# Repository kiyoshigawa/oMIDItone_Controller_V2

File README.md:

This is a refactored and updated version of the code in the https://github.com/kiyoshigawa/oMIDItone github repo intended to simplify and make faster the existing code base while simultaneously switching to PlatformIO.

It is code written to run a 6-head MIDI controlled Otamatone synth, including lighting and mouth opening/closing servo animations. The project is running on a Teensy 3.2, using the arduino framework through PlatformIO, and is using the following libraries in addition to the libraries that I have written myself specifically for this project:
https://github.com/adafruit/Adafruit_NeoPixel 
https://github.com/adafruit/Adafruit-PWM-Servo-Driver-Library (Modified to work with i2c_t3.h)
https://github.com/nox771/i2c_t3
https://github.com/pedvide/ADC

The updated version is reworked to make handling MIDI it's own MIDIController class, as well as to simplify the oMIDItone object class to operate based only on desired frequencies instead of handling MIDI notes, pitch bends, etc.

This readme information will be lagging behind the actual development of the code base until it is nearly done and working properly, so look for more up-to-date comments in the source files for the time being. Once the project is working properly and unlikely to ahve significant changes, I will add a better writeup of everything here.

All my code is being released under the GPLV3 unless otherwise noted in the included third party libraries that the project is built on.

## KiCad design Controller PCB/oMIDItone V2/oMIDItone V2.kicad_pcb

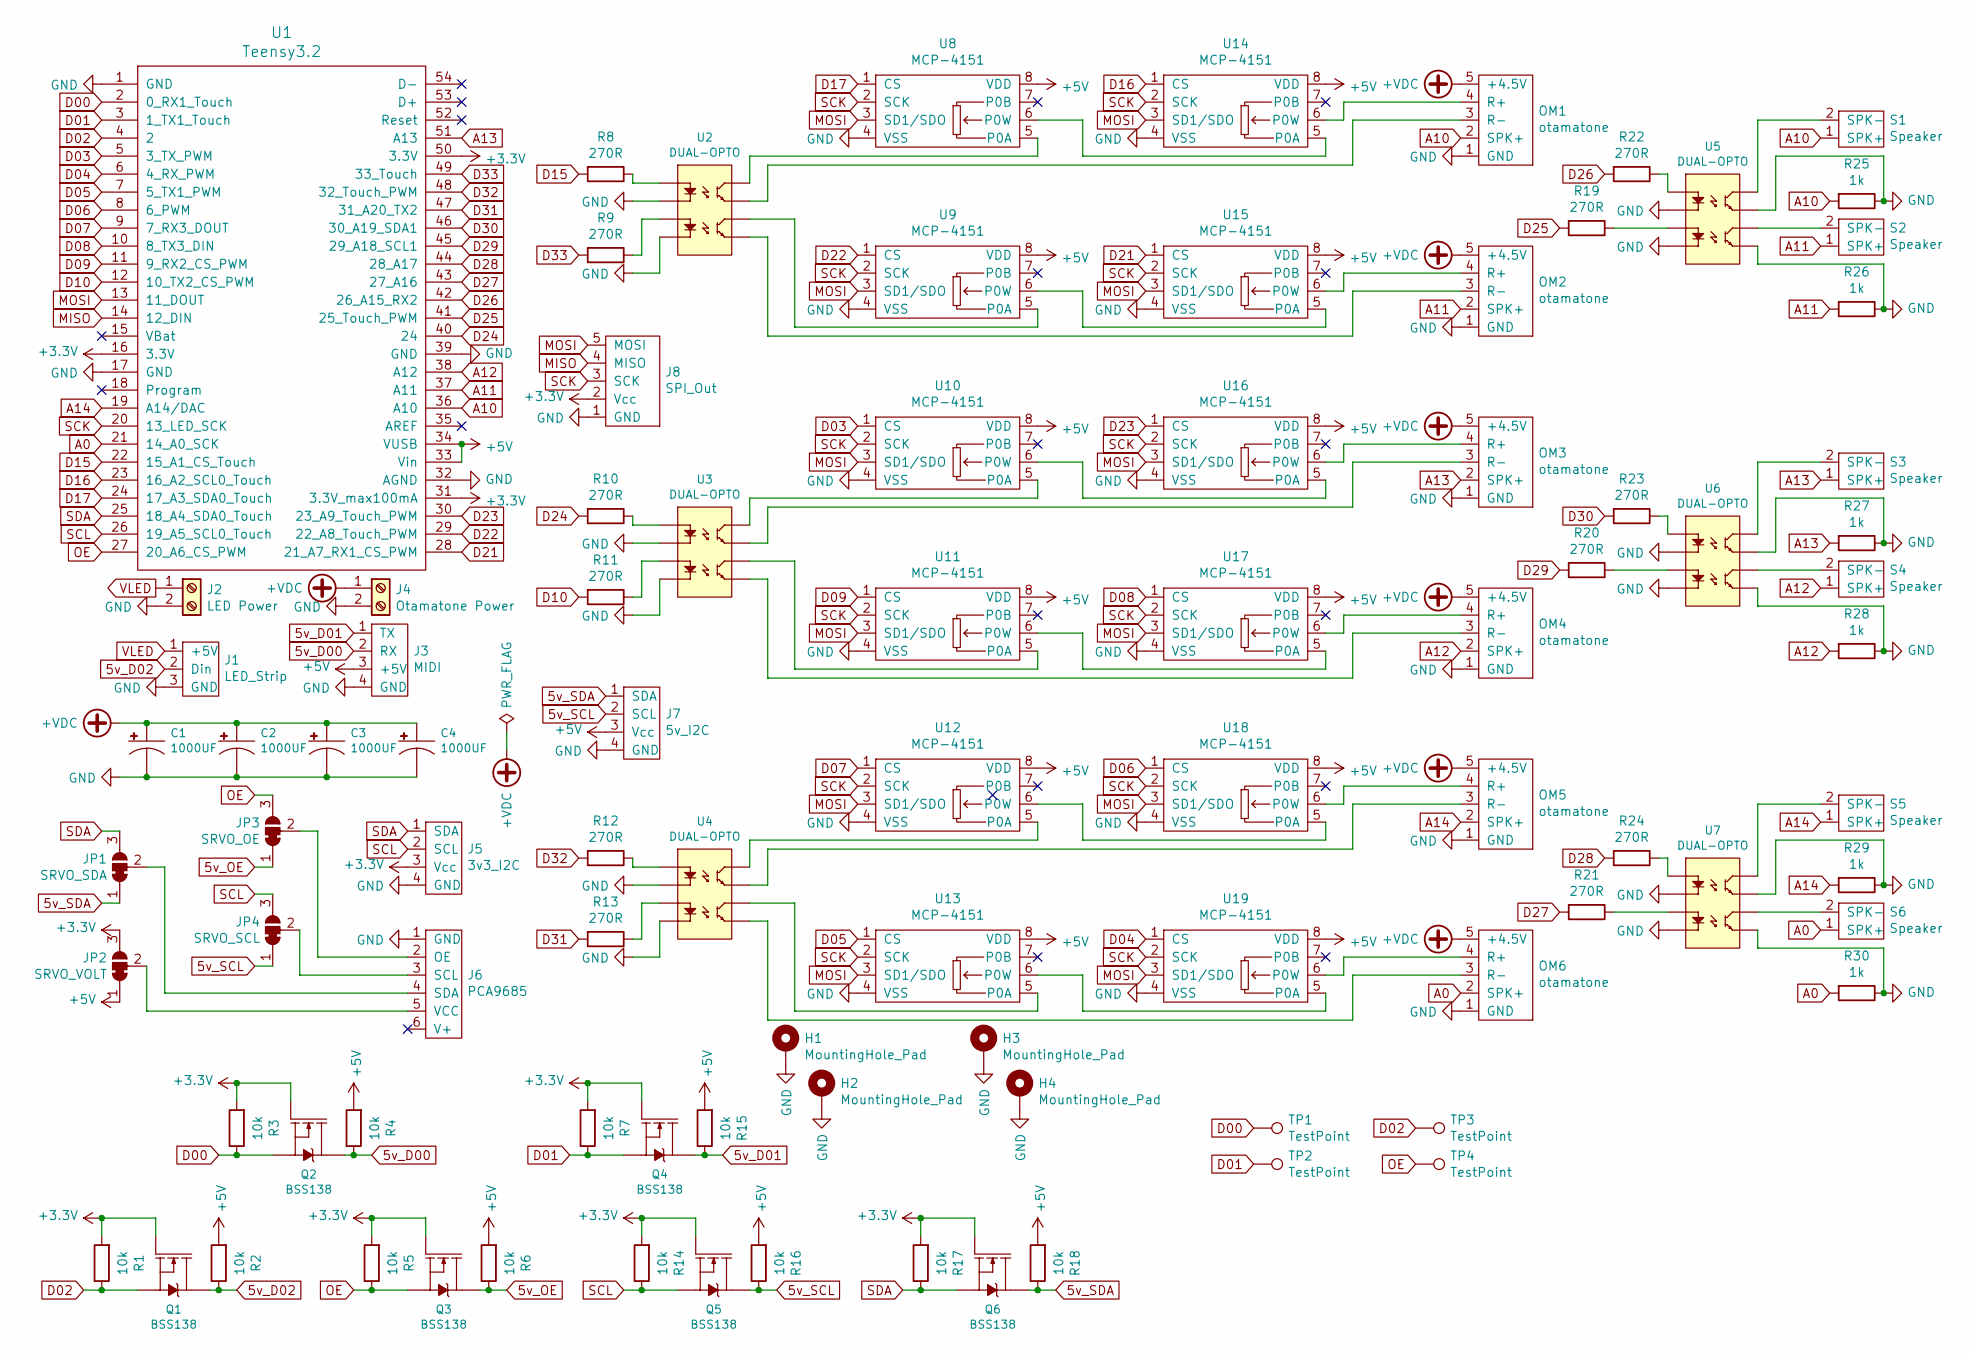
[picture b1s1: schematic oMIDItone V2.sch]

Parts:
C1, C2, C3, C4: 1000UF; CPOL-RADIAL-5MM-10MM-KIT
H1, H2, H3, H4: MountingHole_Pad; MountingHole_3mm_Pad_Via
J1: LED_Strip; PinHeader_1x03_P2.54mm_Vertical
J2: LED Power; PinHeader_1x02_P2.54mm_Vertical
J3: MIDI; PinHeader_1x04_P2.54mm_Vertical
J4: Otamatone Power; PinHeader_1x02_P2.54mm_Vertical
J5: 3v3_I2C; PinHeader_1x04_P2.54mm_Vertical
J6: PCA9685; PinHeader_1x06_P2.54mm_Vertical
J7: 5v_I2C; PinHeader_1x04_P2.54mm_Vertical
J8: SPI_Out; PinHeader_1x05_P2.54mm_Vertical
JP1: SRVO_SDA; SolderJumper-3_P1.3mm_Bridged12_Pad1.0x1.5mm
JP2: SRVO_VOLT; SolderJumper-3_P1.3mm_Bridged12_Pad1.0x1.5mm
JP3: SRVO_OE; SolderJumper-3_P1.3mm_Bridged12_Pad1.0x1.5mm
JP4: SRVO_SCL; SolderJumper-3_P1.3mm_Bridged12_Pad1.0x1.5mm
OM1, OM2, OM3, OM4, OM5, OM6: otamatone; PinHeader_1x05_P2.54mm_Vertical
Q1, Q2, Q3, Q4, Q5, Q6: BSS138; SOT-23
R1, R2, R3, R4, R5, R6, R7, R14, R15, R16, R17, R18: 10k; R_0603_1608Metric
R8, R9, R10, R11, R12, R13, R19, R20, R21, R22, R23, R24: 270R; R_0603_1608Metric
R25, R26, R27, R28, R29, R30: 1k; R_0603_1608Metric
S1, S2, S3, S4, S5, S6: Speaker; PinHeader_1x02_P2.54mm_Vertical
TP1, TP2, TP3, TP4: TestPoint; Test_Point_Keystone_5019_Minature
U1: Teensy3.2; Teensy30_31_32_LC
U2, U3, U4, U5, U6, U7: DUAL-OPTO; SOIC-8_3.9x4.9mm_P1.27mm
U8, U9, U10, U11, U12, U13, U14, U15, U16, U17, U18, U19: MCP-4151; SOIC-8_3.9x4.9mm_P1.27mm

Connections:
5v_D00: J3.2 (RX), Q2.3 (D), R4.1
5v_D01: J3.1 (TX), Q4.3 (D), R15.1
5v_D02: J1.2 (Din), Q1.3 (D), R2.1
5v_OE: JP3.1 (A), Q3.3 (D), R6.1
5v_SCL: J7.2 (SCL), JP4.1 (A), Q5.3 (D), R16.1
5v_SDA: J7.1 (SDA), JP1.1 (A), Q6.3 (D), R18.1
+3V3: J5.3 (Vcc), J8.2 (Vcc), JP2.3 (B), Q1.1 (G), Q2.1 (G), Q3.1 (G), Q4.1 (G), Q5.1 (G), Q6.1 (G), R1.2, R3.2, R5.2, R7.2, R14.2, R17.2, U1.16 (3.3V), U1.31 (3.3V_max100mA), U1.50 (3.3V)
+5V: J3.3 (+5V), J7.3 (Vcc), JP2.1 (A), R2.2, R4.2, R6.2, R15.2, R16.2, R18.2, U1.33 (Vin), U1.34 (VUSB), U8.8 (VDD), U9.8 (VDD), U10.8 (VDD), U11.8 (VDD), U12.8 (VDD), U13.8 (VDD), U14.8 (VDD), U15.8 (VDD), U16.8 (VDD), U17.8 (VDD), U18.8 (VDD), U19.8 (VDD)
+VDC: C1.+, C2.+, C3.+, C4.+, J4.1, OM1.5 (+4.5V), OM2.5 (+4.5V), OM3.5 (+4.5V), OM4.5 (+4.5V), OM5.5 (+4.5V), OM6.5 (+4.5V)
A0: OM6.2 (SPK+), R30.2, S6.1 (SPK+), U1.21 (14_A0_SCK)
A10: OM1.2 (SPK+), R25.2, S1.1 (SPK+), U1.36 (A10)
A11: OM2.2 (SPK+), R26.2, S2.1 (SPK+), U1.37 (A11)
A12: OM4.2 (SPK+), R28.2, S4.1 (SPK+), U1.38 (A12)
A13: OM3.2 (SPK+), R27.2, S3.1 (SPK+), U1.51 (A13)
A14: OM5.2 (SPK+), R29.2, S5.1 (SPK+), U1.19 (A14/DAC)
D00: Q2.2 (S), R3.1, TP1.1, U1.2 (0_RX1_Touch)
D01: Q4.2 (S), R7.1, TP2.1, U1.3 (1_TX1_Touch)
D02: Q1.2 (S), R1.1, TP3.1, U1.4 (2)
D03: U1.5 (3_TX_PWM), U10.1 (CS)
D04: U1.6 (4_RX_PWM), U19.1 (CS)
D05: U1.7 (5_TX1_PWM), U13.1 (CS)
D06: U1.8 (6_PWM), U18.1 (CS)
D07: U1.9 (7_RX3_DOUT), U12.1 (CS)
D08: U1.10 (8_TX3_DIN), U17.1 (CS)
D09: U1.11 (9_RX2_CS_PWM), U11.1 (CS)
D10: R11.2, U1.12 (10_TX2_CS_PWM)
D15: R8.2, U1.22 (15_A1_CS_Touch)
D16: U1.23 (16_A2_SCL0_Touch), U14.1 (CS)
D17: U1.24 (17_A3_SDA0_Touch), U8.1 (CS)
D21: U1.28 (21_A7_RX1_CS_PWM), U15.1 (CS)
D22: U1.29 (22_A8_Touch_PWM), U9.1 (CS)
D23: U1.30 (23_A9_Touch_PWM), U16.1 (CS)
D24: R10.2, U1.40 (24)
D25: R19.2, U1.41 (25_Touch_PWM)
D26: R22.2, U1.42 (26_A15_RX2)
D27: R21.2, U1.43 (27_A16)
D28: R24.2, U1.44 (28_A17)
D29: R20.2, U1.45 (29_A18_SCL1)
D30: R23.2, U1.46 (30_A19_SDA1)
D31: R13.2, U1.47 (31_A20_TX2)
D32: R12.2, U1.48 (32_Touch_PWM)
D33: R9.2, U1.49 (33_Touch)
GND: C1.-, C2.-, C3.-, C4.-, H1.1, H2.1, H3.1, H4.1, J1.3 (GND), J2.2, J3.4 (GND), J4.2, J5.4 (GND), J6.1 (GND), J7.4 (GND), J8.1 (GND), OM1.1 (GND), OM2.1 (GND), OM3.1 (GND), OM4.1 (GND), OM5.1 (GND), OM6.1 (GND), R25.1, R26.1, R27.1, R28.1, R29.1, R30.1, U1.1 (GND), U1.17 (GND), U1.32 (AGND), U1.39 (GND), U2.2 (C1), U2.4 (C2), U3.2 (C1), U3.4 (C2), U4.2 (C1), U4.4 (C2), U5.2 (C1), U5.4 (C2), U5.5 (EM2), U5.7 (EM1), U6.2 (C1), U6.4 (C2), U6.5 (EM2), U6.7 (EM1), U7.2 (C1), U7.4 (C2), U7.5 (EM2), U7.7 (EM1), U8.4 (VSS), U9.4 (VSS), U10.4 (VSS), U11.4 (VSS), U12.4 (VSS), U13.4 (VSS), U14.4 (VSS), U15.4 (VSS), U16.4 (VSS), U17.4 (VSS), U18.4 (VSS), U19.4 (VSS)
MISO: J8.4 (MISO), U1.14 (12_DIN)
MOSI: J8.5 (MOSI), U1.13 (11_DOUT), U8.3 (SD1/SDO), U9.3 (SD1/SDO), U10.3 (SD1/SDO), U11.3 (SD1/SDO), U12.3 (SD1/SDO), U13.3 (SD1/SDO), U14.3 (SD1/SDO), U15.3 (SD1/SDO), U16.3 (SD1/SDO), U17.3 (SD1/SDO), U18.3 (SD1/SDO), U19.3 (SD1/SDO)
unnamed: J6.2 (OE), JP3.2 (C)
unnamed: J6.3 (SCL), JP4.2 (C)
unnamed: J6.4 (SDA), JP1.2 (C)
unnamed: J6.5 (VCC), JP2.2 (C)
unnamed: OM1.3 (R-), U2.7 (EM1)
unnamed: OM1.4 (R+), U14.6 (P0W)
unnamed: OM2.3 (R-), U2.5 (EM2)
unnamed: OM2.4 (R+), U15.6 (P0W)
unnamed: OM3.3 (R-), U3.7 (EM1)
unnamed: OM3.4 (R+), U16.6 (P0W)
unnamed: OM4.3 (R-), U3.5 (EM2)
unnamed: OM4.4 (R+), U17.6 (P0W)
unnamed: OM5.3 (R-), U4.7 (EM1)
unnamed: OM5.4 (R+), U18.6 (P0W)
unnamed: OM6.3 (R-), U4.5 (EM2)
unnamed: OM6.4 (R+), U19.6 (P0W)
unnamed: R8.1, U2.1 (A1)
unnamed: R9.1, U2.3 (A2)
unnamed: R10.1, U3.1 (A1)
unnamed: R11.1, U3.3 (A2)
unnamed: R12.1, U4.1 (A1)
unnamed: R13.1, U4.3 (A2)
unnamed: R19.1, U5.3 (A2)
unnamed: R20.1, U6.3 (A2)
unnamed: R21.1, U7.3 (A2)
unnamed: R22.1, U5.1 (A1)
unnamed: R23.1, U6.1 (A1)
unnamed: R24.1, U7.1 (A1)
unnamed: S1.2 (SPK-), U5.8 (CL1)
unnamed: S2.2 (SPK-), U5.6 (CL2)
unnamed: S3.2 (SPK-), U6.8 (CL1)
unnamed: S4.2 (SPK-), U6.6 (CL2)
unnamed: S5.2 (SPK-), U7.8 (CL1)
unnamed: S6.2 (SPK-), U7.6 (CL2)
unnamed: U2.6 (CL2), U9.5 (P0A)
unnamed: U2.8 (CL1), U8.5 (P0A)
unnamed: U3.8 (CL1), U10.5 (P0A)
unnamed: U10.6 (P0W), U16.5 (P0A)
unnamed: U3.6 (CL2), U11.5 (P0A)
unnamed: U11.6 (P0W), U17.5 (P0A)
unnamed: U4.8 (CL1), U12.5 (P0A)
unnamed: U12.6 (P0W), U18.5 (P0A)
unnamed: U4.6 (CL2), U13.5 (P0A)
unnamed: U13.6 (P0W), U19.5 (P0A)
unnamed: U8.6 (P0W), U14.5 (P0A)
unnamed: U9.6 (P0W), U15.5 (P0A)
OE: JP3.3 (B), Q3.2 (S), R5.1, TP4.1, U1.27 (20_A6_CS_PWM)
SCK: J8.3 (SCK), U1.20 (13_LED_SCK), U8.2 (SCK), U9.2 (SCK), U10.2 (SCK), U11.2 (SCK), U12.2 (SCK), U13.2 (SCK), U14.2 (SCK), U15.2 (SCK), U16.2 (SCK), U17.2 (SCK), U18.2 (SCK), U19.2 (SCK)
SCL: J5.2 (SCL), JP4.3 (B), Q5.2 (S), R14.1, U1.26 (19_A5_SCL0_Touch)
SDA: J5.1 (SDA), JP1.3 (B), Q6.2 (S), R17.1, U1.25 (18_A4_SDA0_Touch)
VLED: J1.1 (+5V), J2.1

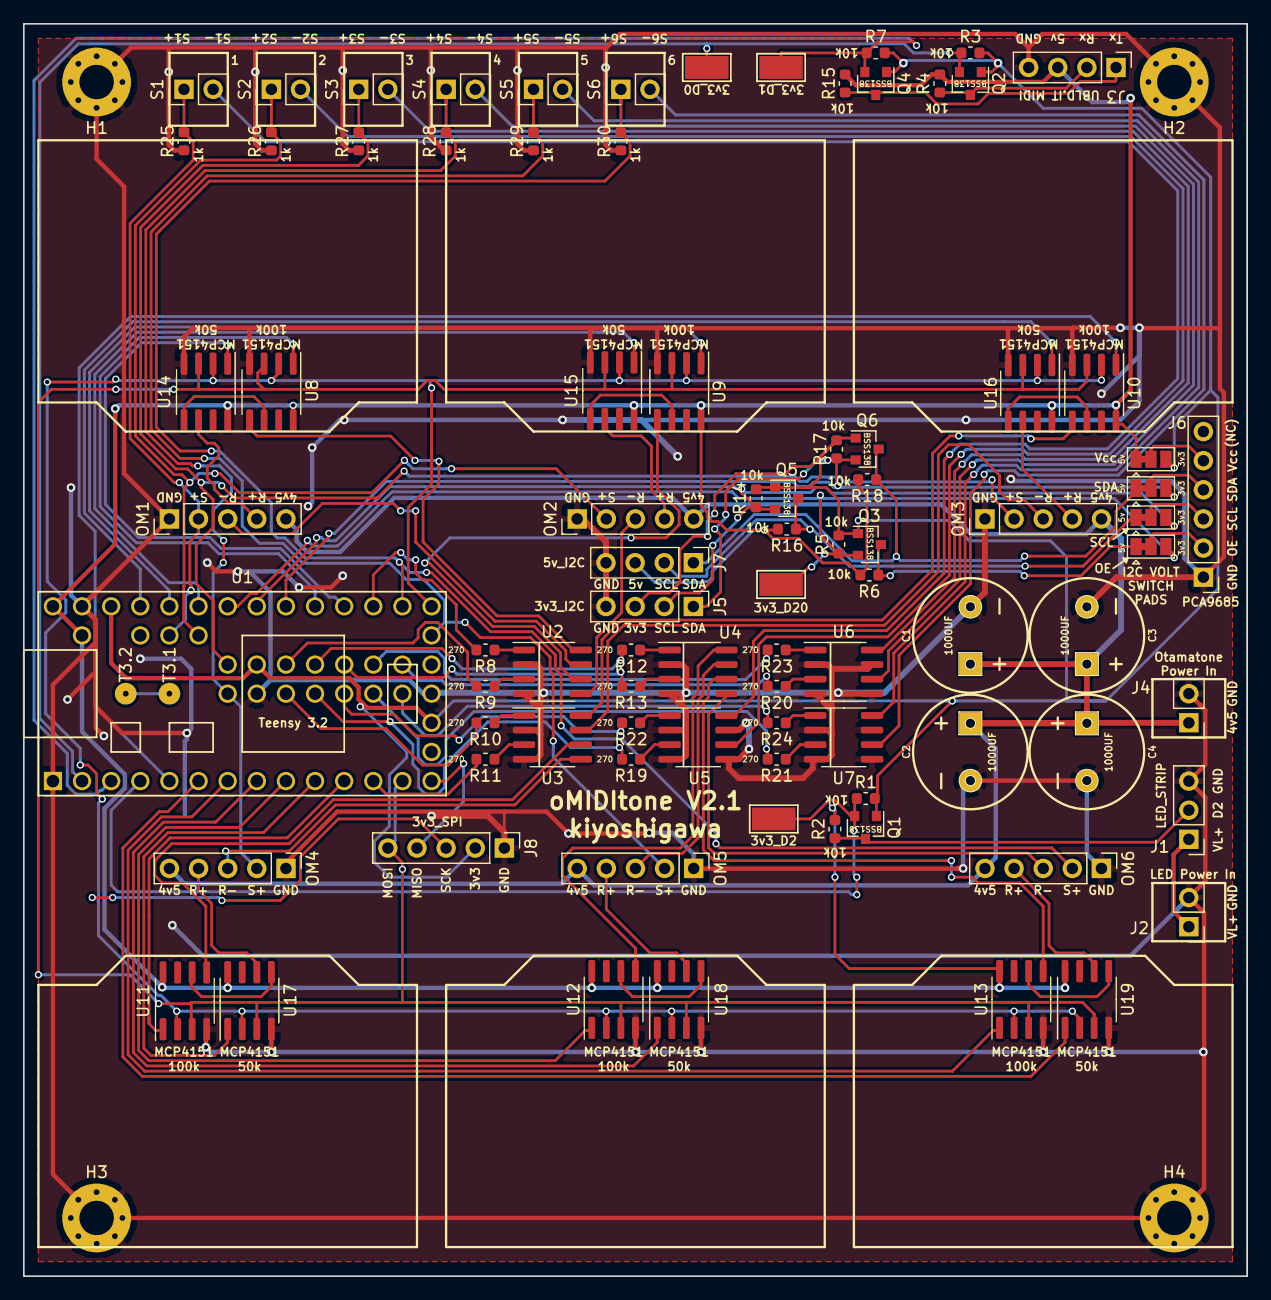
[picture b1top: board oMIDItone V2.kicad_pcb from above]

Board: 2 copper layers, 106.7 x 109.2 mm, 91 parts (0 on the bottom side), 96 nets.

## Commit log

2019-12-03 Initial Commit with 3rd Party Libraries
2019-12-03 added old unchanged oMIDItone project libraries
2019-12-03 old libraries compile properly now
2019-12-03 Weirdness with Adafruit Servo Git Commits Fixed
2019-12-03 First untested attempt at fixing oMIDItone class
2019-12-03 Skeletal Main Code without MIDI yet.
2019-12-03 cleaned up function brackets
2019-12-03 removed unused include folder
2019-12-04 more or less functional oMIDItone class
2019-12-05 Lighting Controller to enums and switches
2019-12-05 MIDIController basics w/ hardware+usbMIDI handlers
2019-12-10 Expanding on MIDI handling - Debut outputs added
2019-12-10 Fixed Overflow Issues with add_note and remove_note
2019-12-12 added CC handler functions, CC120-127 defaults working
2019-12-12 RPN Handler functions set up
2019-12-13 pitch bending and max pitch bend RPNs functional
2019-12-13 Error cleanup and staging for head assignments
2019-12-13 reverted to global tuning array, not enough RAM
2019-12-14 CC handler functions added
2019-12-14 fixed some CC handling bugs after testing
2019-12-14 moved validate functions to lighting controller
2019-12-15 crashing when playing notes - debugging
2019-12-15 fixed freq_reading_index out of bounds error
2019-12-15 pitch correction fixed topping and bottoming out
2019-12-15 Finally back to feature parity with oMIDItone V1
2019-12-16 Bug Fixes.
2019-12-16 Re-implemented per-channel tuning support
2019-12-17 Made global tuning toggleable with a #define
2019-12-22 Cleaned up #define names with per-class prefixes
2019-12-22 MIDIController Comments cleaned up.
2019-12-22 oMIDItone class comment cleanup
2019-12-22 updated lighting controller comments.
2019-12-22 main comment update
2019-12-22 Removed free_mem() function, no longer needed.
2019-12-22 Cleaned up TODO: messages
2020-08-29 Replaced bad servos, updated resting positions.
